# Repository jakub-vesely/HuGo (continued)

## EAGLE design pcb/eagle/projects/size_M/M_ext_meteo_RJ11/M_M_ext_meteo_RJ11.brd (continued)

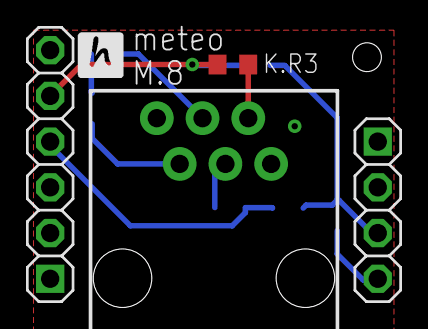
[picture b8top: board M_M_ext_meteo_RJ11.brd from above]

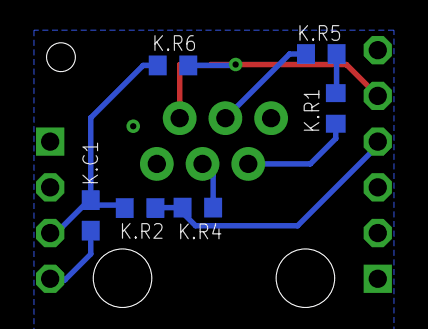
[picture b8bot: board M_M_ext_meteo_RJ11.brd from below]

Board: 2 copper layers, 10 parts (6 on the bottom side), 8 nets.

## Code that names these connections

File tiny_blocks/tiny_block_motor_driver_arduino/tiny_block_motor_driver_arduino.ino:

/*
power board management

BOARD: base+power
Chip: ATtiny414
Clock Speed: 10MHz
Programmer: jtag2updi (megaTinyCore)
*/

void HugoTinyWireProcessCommand(uint8_t command, uint8_t payload_size);
void HugoTinyWireFillModuleVersion();

#include <Wire.h>
#include <avr/sleep.h>

#include <hugo_tiny_wire.h>
#include <hugo_defines.h>
#include "motor.h"

#define PCB_VERSION 2

#define INA1 PIN_PA5
#define INB1 PIN_PB2
#define FOTO1 PIN_PA6

#define INA2 PIN_PA3
#define INB2 PIN_PA4
#define FOTO2 PIN_PA2

# define SENSOR_LED PIN_PB3

static Motor motor1(INA1, INB1, FOTO1);
static Motor motor2(INA2, INB2, FOTO2);

static uint8_t s_loop_counter = 0;
static uint8_t s_pwm_period = 10; //10 is equal to 100us

void sensor1Interrupt(){
  motor1.incrementCounter();
}

void sensor2Interrupt(){
  motor2.incrementCounter();
}

void HugoTinyWireProcessCommand(uint8_t command, uint8_t payload_size) {
    switch (command){
    case I2C_MOTOR_POWER_ON:
      digitalWrite(SENSOR_LED, HIGH);
      break;
    case I2C_MOTOR_POWER_OFF:
      digitalWrite(SENSOR_LED, LOW);
      break;
    case I2C_MOTOR_SET_PWM_PERIOD:
      if (payload_size == 1){
        s_pwm_period = Wire.read();
      }
      break;
    default:
      if (payload_size > 0){
        uint8_t motor_id = Wire.read();
        uint8_t extra_byte = 0;
        if (payload_size == 2){
          extra_byte = Wire.read();
        }
        if (motor_id == 1){
          motor1.processCommand(command, extra_byte, s_buffer);
        }
        else if (motor_id == 2){
          motor2.processCommand(command, extra_byte, s_buffer);
        }
      } 
    }
}

void HugoTinyWireFillModuleVersion(){
  s_buffer.data[0] = I2C_BLOCK_TYPE_ID_MOTOR_DRIVER;
  s_buffer.data[1] = PCB_VERSION;
  s_buffer.data[2] = 0;
  s_buffer.size = 3;
}

void setup(){
  attachInterrupt(digitalPinToInterrupt(FOTO1), sensor1Interrupt, CHANGE); //must be static fuction (can't be part of the motor class)
  attachInterrupt(digitalPinToInterrupt(FOTO2), sensor2Interrupt, CHANGE);

  pinMode(SENSOR_LED, OUTPUT);
  digitalWrite(SENSOR_LED, LOW);
    
  HugoTinyWireInitialize(I2C_BLOCK_TYPE_ID_MOTOR_DRIVER, NULL);
}

void loop(){
  motor1.processLoopIteration(s_loop_counter);
  motor2.processLoopIteration(s_loop_counter);

  s_loop_counter++;
  if (s_loop_counter > 99){
    s_loop_counter = 0;
  }

  delayMicroseconds((uint16_t)s_pwm_period * 10); //one pwm_period step is 10 us
}

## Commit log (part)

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2020-05-24 simple example (proof of concept) of calling LUA code from esp-idf C code. It seems it will work and intended SW design is possible.
2020-05-24 added first module build_in_led with one method main stack has be increased because 7 was too low to call "require" package
2020-05-27 copying LUA files from binary data to spiffs is automated - process_lua_files.py generate .c/.h files during when .lua files are added to CmakeList.txt
2020-05-28 added visualization
2020-05-29 added event loop + adjusted cmake
2020-05-29 added possible module connector layouts
2020-05-30 modules files are split in base of modules now
2020-05-30 rename variables in base of files
2020-06-03 refactoring: naming convention * prefix cl_<module_name>_* for functions transferred from c to lua * prefix hugo_<module_name>_* for public funcntions * include <> for files searched in include direc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
    added a few macros for repetitive code
    built-in led is based on the gpio module
2020-06-04 added functionality for chassis + fixed typo
2020-06-06 Added ir_remote module -> remote controlled car
2020-06-24 added tests for timer and gpio - it is used built in unity test framework, for gpio testing is used the fff mock framework
2020-06-25 external sources moved to externals directory
2020-07-22 implemented base functionality ssd1306 display
2020-07-27 i2c_wrapper renamed to i2c because there is no conflict with ESP's i2c driver + minor fixes
2020-07-27 graphical design
2020-11-04 removed mpu9250 and arduino-esp32 - will be inserted as a submodule
2020-11-28 I2C messages are processed over event loop - prevent conflicts
2020-12-14 added RGB LED code for attiny412 placed in separate block
2020-12-14 updated block connector analysis file
2020-12-14 added PCB designs
2020-12-31 completed pcb design for M.0 - made PCB order
2021-01-02 added logo to readme
2021-01-15 changes in pcb desingm - not finished and another minor changes in the documentation
2021-02-04 pcb M.1 -not finished
2021-02-04 fix for esp board (RST -> RTS)
2021-02-28 updated logo
2021-02-28 updateed PCBs - adjustments based on usage of version 1
2021-02-28 repository reorganisation .ino are sored in appropriate esp components
2021-03-01 finishd the motor block implemention
2021-03-13 stored shells - not finished yet
2021-03-16 base3x4
2021-03-19 rotation sensor base
2021-04-02 updated 3x4 shell
2021-04-02 adjusted 90° connector postition to be possible to cut to 1x3 easyly
2021-04-16 chassis adjustments to version H2
2021-05-10 updated PCBS after the version 1 delivery
2021-05-10 removed unused chassis (renamed to hugo framework) + added stl to ignored file types
2021-05-22 repository structure reorganized (tiny-blocks moved to a separate directory) implemented tiny-power-block
2021-05-22 updated PCBs after delivery of v1
2021-05-22 added shels for led and top-open blocks updated hugo-framework
2021-06-23 updated PCBs for version 2
2021-06-23 shell storage refactoring - created folder tiny-blocks added opened shell + extensions
2021-07-23 ble support + downloading lua files
2021-08-21 added datasheet for mp3 processor
2021-09-02 added micropython submodule - no functionality implemented
2021-09-28 added forked micropython as a submodue
2021-10-02 added support for ssd1306 - without appropriate tiny block
2021-10-02 tiny blodk sources moved out of the deprecated src
2021-10-06 updated display and rgb_led blocks
2021-10-06 improved BLE uploading
2021-10-06 added simple example of events.py
2021-10-24 ble keyboard (remote control)
2021-10-27 updated power module to be handled charging correctly (LED + attiny pin)
2021-11-12 added python code for power block refactoring i2c calls - run until complete doesn't work from async environment. improved active variable lot of small improvements adjusted another toold to be adjus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
2021-12-05 motor_driver + a few improvements
2021-12-27 button block + chassis + default i2c addresses
2021-12-28 inverted logic of power switch to be left for off and right for on
2021-12-29 bugfixes: non-repetitive mode for ActiveVariabl + block types feature: available block - is_available() - program is not terminated immediatelly when an used block is not available
2021-12-31 mem_info + finished minner_game
2021-12-31 hugo project python files are precompiled to .mpy files now
2022-01-02 simplified chassis functionality
2022-01-09 > power sabing by calling light_sleep + a few frormal changes
2022-01-22 added Smoother class, it should limit a sensor noise. RAM consumtion optimization
2022-01-29 updated main board - added 5 to 3.3V regulator becaues one in CP is too weak updated power board - added shotky diode to FET to be sure it works as expected
2022-01-29 .pyc files as builded are ignored
2022-01-29 shell cleanup
2022-02-10 basic autonomous movement for rover + a few improvements in the micropython Hugo modules.
2022-03-05 added ir block simplified active variable getter setter names refactored virtua keyboard added support for multilevel file system moved tiny_blocks (to src) root directory for paths is src
2022-03-06 restructuralized src - files moved to subdirectories fixed examples
2022-03-30 added simple dock
2022-03-30 added sound top
2022-03-30 improved python building (is built what is new only)
2022-03-30 minor changes in Arduino common code
2022-04-03 bugfix: when user built two different project files from another could remains in .build folder removed unused import (inserted probably automatically by IDE)
2022-04-15 sound block implementation + a few fixes in active_variable (task was not removed for not repeating tasks)sound block and
2022-04-15 moved sd-card closer to border - it was difficult to insert it.
2022-04-22 finishing PCB release M.v3 - not done yet
2022-05-18 PCB M.3
2022-06-01 main and switch pcbs adjusted
2022-07-04 power ext board adjustments - mainly replacement of charging info MOSFET - PMOS to NMOS switch position adjustment
2022-07-04 adapter board with AtTiny-414
2022-07-04 bugfix: USB flag while charging
2022-07-04 simplified devel "example"
2022-07-04 hugo_terminal refactoring - split to files by classes
2022-07-10 removed unnecessary log info
2022-07-10 hugo terminal gui based on kivy
2022-08-05 updated micropython fork from upstream fixed appeared issues ble config rxbuf is not supported any more SHELL_STOP_PROGRAM doesn't return value - added timeout
2022-08-05 removed quantities example - it is actually updated power block example
2022-08-23 remote value is a special log message now + > remote value - ble and shell issues causing rebootings and crashes > remote values - crashing when hugo_terminal waiting for BLE
2022-09-16 updated for PCB version 4
2022-09-26 bugfixes: * in case of restart from ble, program starts after ble is connected again to be all logs provided to HugoTerminal * verbose logs just in case they are required * logs
    features:
    * files used in the project are imported only
2022-09-26 collection of PCBs for v4 started
2022-09-29 added ignore_same attribute. fixed active_variable test
2022-10-25 PCB v4
2022-10-29 version without most of milling
2023-01-02 not finished meteo block
2023-01-02 minor fixes
2023-01-02 > added BME280
2023-01-12 dashboard support fix no-bluetooth crash
2023-01-14 bugfix: loading local files in examples
2023-01-14 picropython > added meteo block > Merge branch 'micropython:master' into master
2023-01-14 meteo example
2023-02-16 changed one data bit to be compatible with T-micro32+
2023-02-16 3.3V fuse moved before stabilizer to be final voltage as expected 3.3V. the fuse can loose up to 0.3V
2023-02-16 added support for deep sleep with attiny414
2023-06-18 __AVR_ATtiny1614__ can be used as block microcontroler
2023-07-23 pull-up resistors for i2c
2023-07-23 changes in values LM3671_3.3 -> MCP1603T-330I
2023-07-23 3x4 v5 sent to be manufactured
2023-07-23 removed files commited by mistake
2023-07-23 LM3671_3.3 -> MCP1603T-330I attempt with centered USB
2023-07-23 ble extension with 3 different modules
2023-07-31 bugfix: handle case where expected length is 0 and the length is part of the message added ble_block
2023-07-31 fixed Hugo dashboard hierarchy name convention
2023-08-04 who knows
2023-08-18 created tiny_main_base - should contain basic functionality with low power consumtion usage for the tiny_set_meteo app adjusted ble block firmware
2023-09-07 finalized version sending data to hugo-board via BLE mesh network
2023-12-06 changed values of used resistors
2023-12-06 changed type of 3.3V converter back to LM3671
2023-12-19 meteo station finalization - still some adjustments needed
2024-01-07 meteo station finalization
2024-01-15 bugfix: is_charging displayed opposite values
2024-02-29 reboot once a day to clean RAM fragmentation
2024-02-29 default values are not send to cloud
2024-02-29 sleep is already enabled => sleep_cpu should be enough
2024-02-29 added preprocessor switch for diaplay => for easier debugging
2024-02-29 rj12 bugfixes: pin interrupts should be recorded correctly now * including erasing counter and * timestamps during sleep
2024-05-12 bugfix: positive values had wrong value
2024-05-12 better energy management for ambient block
2024-05-12 adjusted tiny_set_meteo to be to ble_shield instead of ble block added support for internal metoe (no wind and rain)
2024-05-27 formal changes
2024-05-27 saving energy by turning-off INA when it is not used
2024-06-04 main with ftdi instead of cp - it is cheaper
2024-07-11 bugfix: decimal digits added to the bultiplier calculation (when is calculated shortest format)
2024-07-11 formal: alignment
2024-07-16 usb moved to be possible to place in connected adapters
2024-07-16 main with cp2102N - must be tested
2024-08-05 reorganized pcb folders
2024-08-18 micropython updated to v1.23.0
2024-08-18 feature: mac addess can be set in : sepatated format as well
2024-09-14 PCB v7 * 14 pin attiny is main adapter chip now. * changed adapter pin meaning (a1-a5, swapped RX-TX, VUSB replaced by A5, top most pin changed from GND to A4) * changed usb chip of main board
2024-10-01 MCP1603T-330I changed to LM3671_3.3
    4u7 moved close to input of LM3671_3.3
2024-10-18 * LED2 is connected to PA7 (was PB3) * GPIO pins renamed to D1 - D5 * fixed MISO typo (should be MOSI for PA1)
2024-10-18 formal change of the project name
2024-10-18 fixed path to be compatible with new version of micropython
2024-10-18 updated resistor values for leds + led test
2024-11-29 adjusted tiny_set_meteo to be more reliable minor fixes for older pcb versions
2024-11-29 bugfix - wrong file name
2024-11-29 bugfix: examples should not import development's files
2024-11-29 previous changes extended to micropython
2025-01-26 changed power sleep transistor to p-channel added tssop version for attiny v2 chips
2025-01-26 added shottky diode to vcc connection of another power block without connected power via USB leads to oscillations
2025-01-26 5way switch - used 5 inputs
2025-03-16 classes related to main module moved to tiny_block_main
2025-03-16 RTC_init moved to hugo_utils
2025-03-16 test program for jdy-25
2025-03-16 test program for servo
2025-03-16 just formal changes
2025-03-16 added servo and step motor types + typo
2025-03-16 fixed forgotten auantity name
2025-03-16 uncomment commented out power pin
2025-03-16 fixed source file name to be aligned with the folder name
2025-03-16 added monitor to the flash script
2025-03-16 bugfix: searching boot.py
2025-05-03 redesigned motor driver
2025-07-21 version 8 main changes * ideal diode separated 3v3 DC-DC to protect it from back current * smaller package of ina 219 * usage of tssop attiny v2 in adapter * and change of PA5 to PB2 with ^ and ~ (or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
2025-08-27 updated ports for PCB v. M8
2025-09-09 just a formal changes
2026-02-10 fixed RX-TX
2026-02-10 power possibilities
2026-02-10 formal. warning silencing
2026-02-13 removed debug code
2026-02-13 mesh data check and confirmation
2026-02-28 just renamed
2026-02-28 added agents for shelly and jdy runinng on raspberry pi
2026-02-28 ambient module can be connected as a shield to the main one - no extra adapter for the ambient module is needed
2026-02-28 maker it executable
2026-02-28 the measurement is performed each 10 sec and is send the round value each 5 mins
2026-03-08 PA4 holds power up. PB2 monitors pressing the power button. The idea is that when user press the power button attiny will hold the power. when user press it second time attiny stops the holding.
2026-03-16 to be sure everything i send before going to sleep
2026-04-06 power module finalizations (M9)
